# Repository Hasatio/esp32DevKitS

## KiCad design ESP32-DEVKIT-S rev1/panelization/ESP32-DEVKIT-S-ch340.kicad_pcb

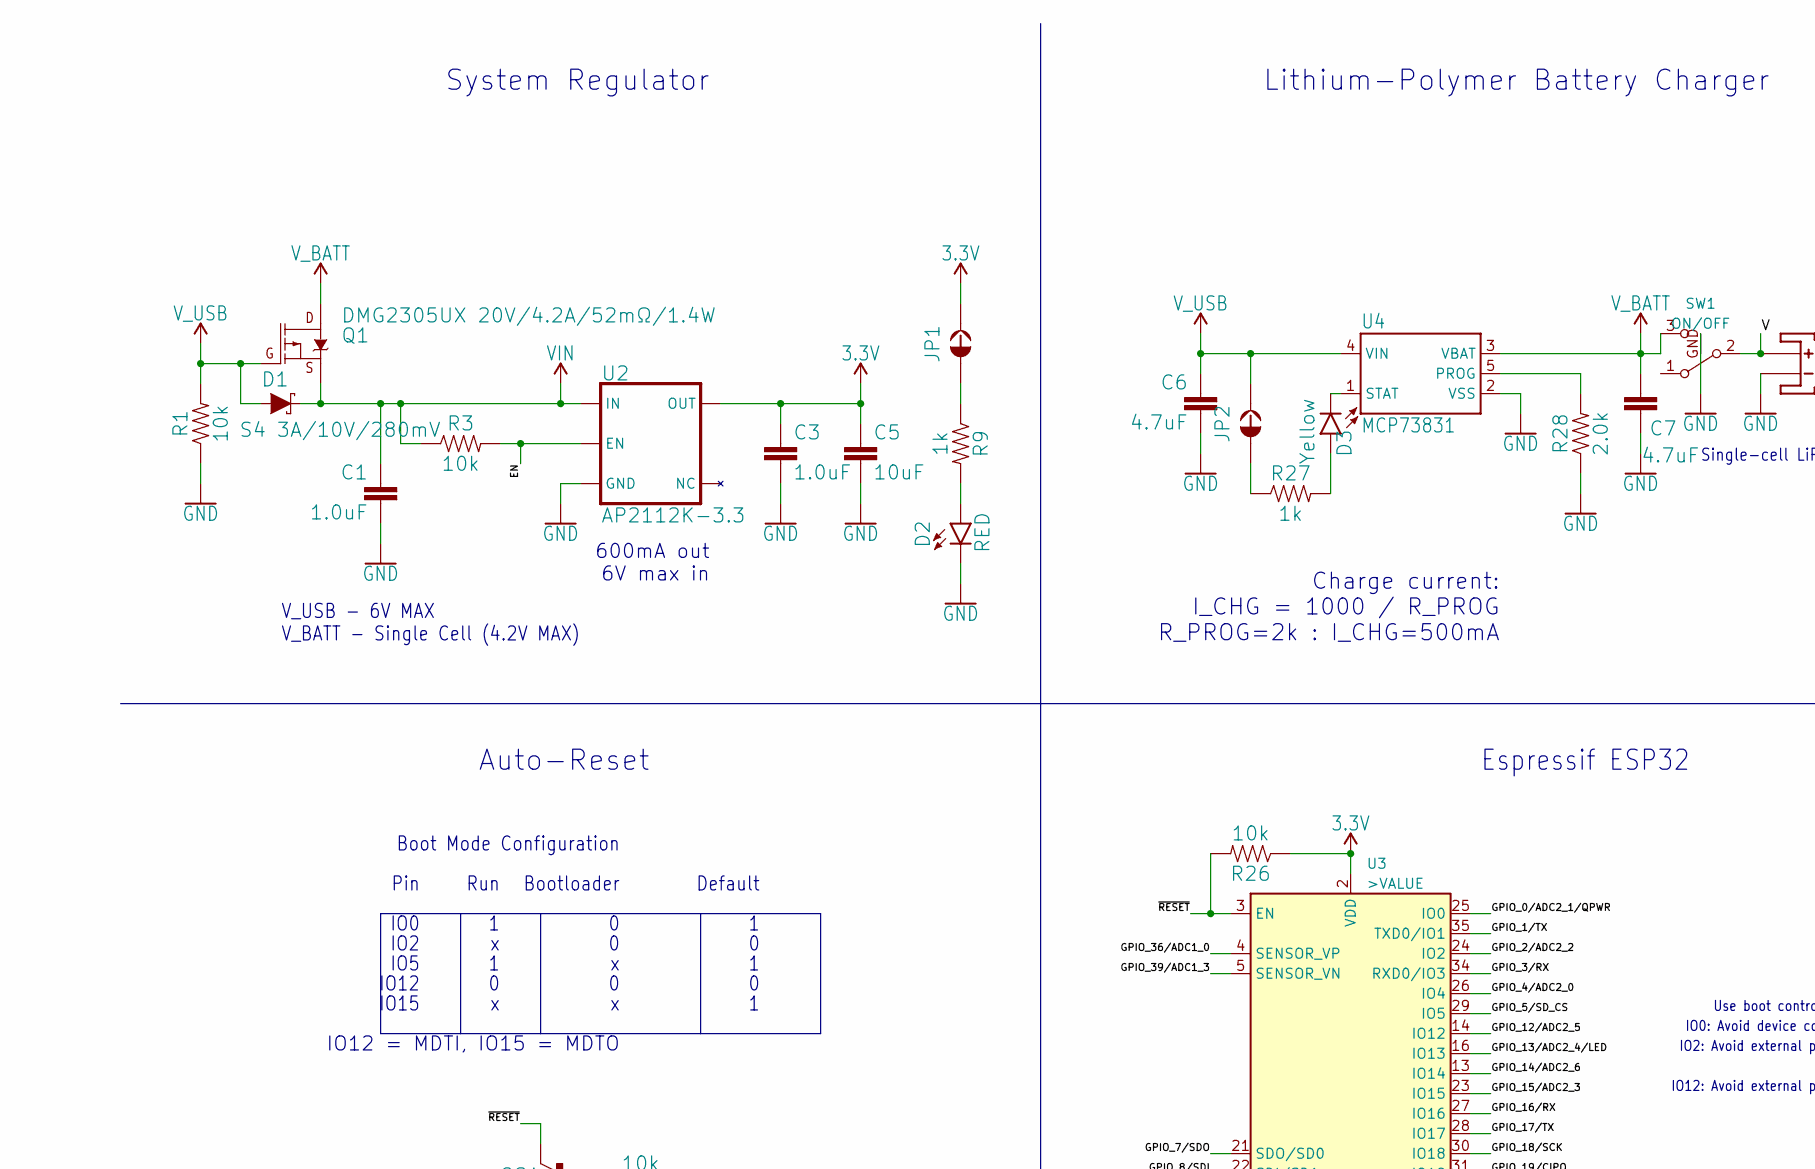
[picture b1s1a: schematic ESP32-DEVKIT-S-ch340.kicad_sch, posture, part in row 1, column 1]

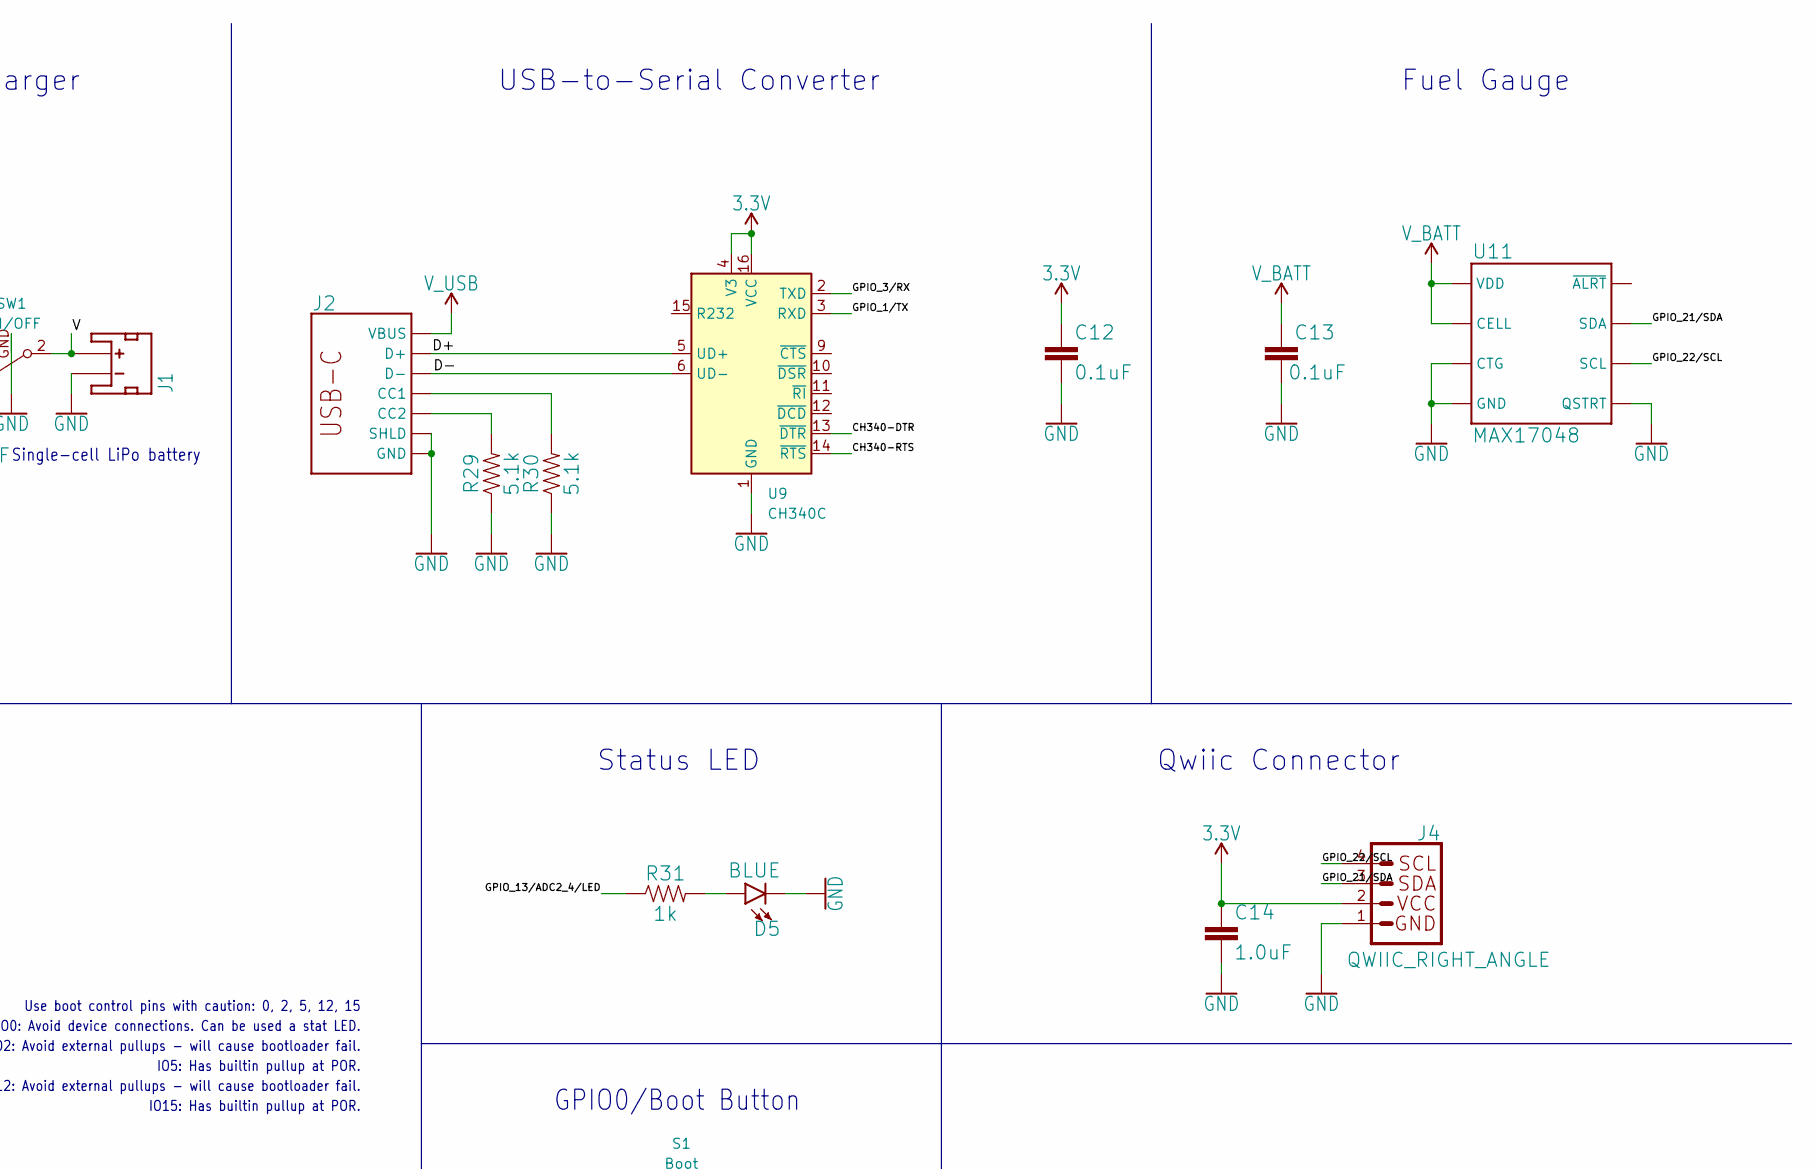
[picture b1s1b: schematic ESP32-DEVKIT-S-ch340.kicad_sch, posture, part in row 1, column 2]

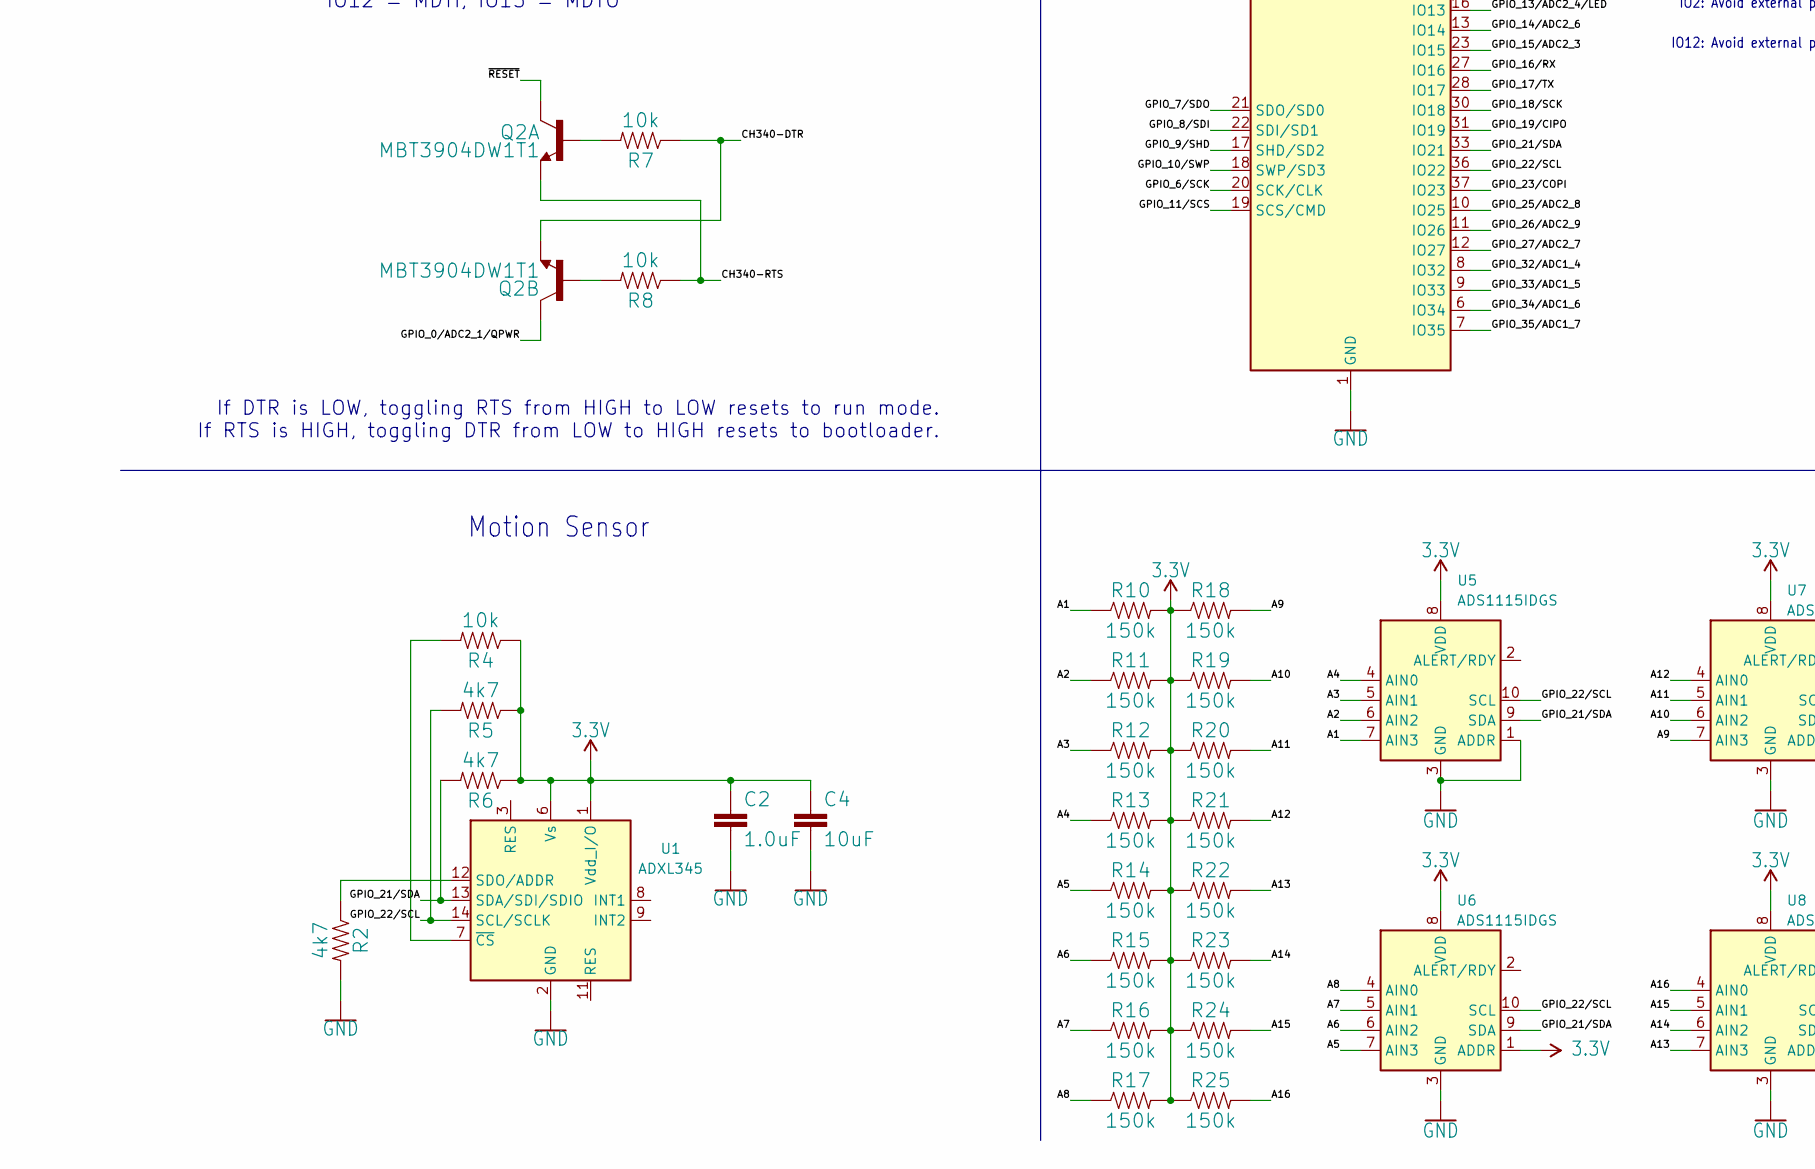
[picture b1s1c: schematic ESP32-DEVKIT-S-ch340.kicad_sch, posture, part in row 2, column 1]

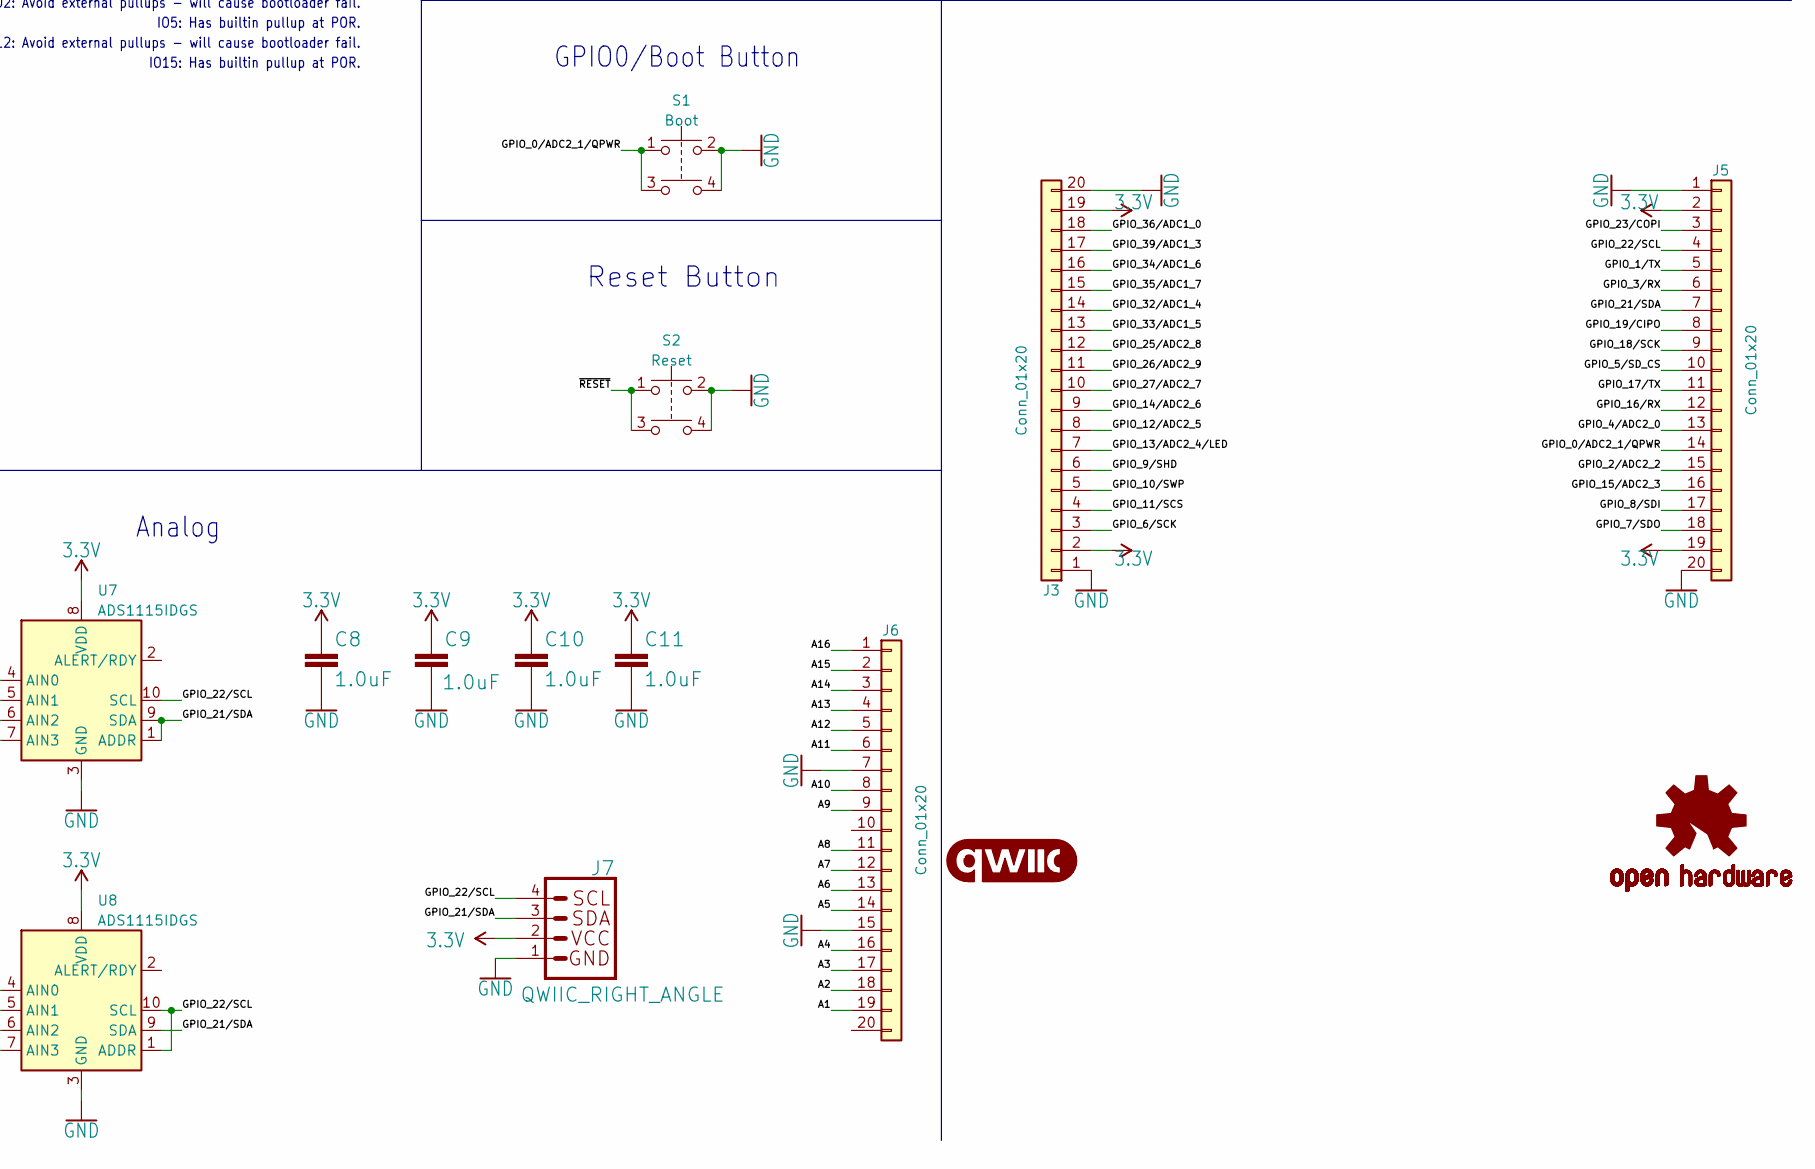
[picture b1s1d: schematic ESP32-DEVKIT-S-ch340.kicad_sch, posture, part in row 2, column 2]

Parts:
C1, C2, C3, C8, C9, C10, C11, C14: 1.0uF; 0402-TIGHT
C4, C5: 10uF; 0402-TIGHT
C6, C7: 4.7uF; 0402-TIGHT
C12, C13: 0.1uF; 0402-TIGHT
D1: S4 3A/10V/280mV; SOD-323
D2: RED; LED-0603
D3: Yellow; LED-0603
D5: BLUE; LED-0603
J1: JST_2MM_MALE; JST-2-SMD
J2: USB_C_2-LAYER_PADS; USB-C-16P-2LAYER-PADS
J3, J5, J6: Conn_01x20; Molex_200528-0200_1x20-1MP_P1.00mm_Horizontal
J4, J7: QWIIC_RIGHT_ANGLE; JST04_1MM_RA
JP1, JP2: JUMPER-SMT_2_NC_TRACE_SILK; SMT-JUMPER_2_NC_TRACE_SILK
LOGO1: QWIIC_LOGO_4MM; QWIIC_4MM
LOGO2: OSHW-LOGOMINI; OSHW-LOGO-MINI
Q1: DMG2305UX 20V/4.2A/52mΩ/1.4W; SOT23-3
Q2: MBT3904DW1T1; SC70-6
R1, R3, R4, R7, R8, R26: 10k; 0402-TIGHT
R2, R5, R6: 4k7; 0402-TIGHT
R9, R27, R31: 1k; 0402-TIGHT
R10, R11, R12, R13, R14, R15, R16, R17, R18, R19, R20, R21, R22, R23, R24, R25: 150k; 0402-TIGHT
R28: 2.0k; 0402-TIGHT
R29, R30: 5.1k; 0402-TIGHT
S1: Boot; TACTILE_SWITCH_SMD_2.8X1.9MM
S2: Reset; TACTILE_SWITCH_SMD_2.8X1.9MM
SW1: ON/OFF; SW_SPDT_k3-1295
U1: ADXL345; LGA-14_3x5mm_P0.8mm_LayoutBorder1x6y
U2: SOT23-5
U3: >VALUE; ESP-WROOM-32-NARROW
U4: MCP73831; SOT23-5
U5, U6, U7, U8: ADS1115IDGS; TSSOP-10_3x3mm_P0.5mm
U9: CH340C; SOIC-16_3.9x9.9mm_P1.27mm
U11: MAX17048; DFN-8

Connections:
3.3V: C2.1, C3.1, C4.1, C5.1, C8.1, C9.1, C10.1, C11.1, C12.1, C14.1, J3.2, J3.19, J4.2, J5.2, J5.19, J7.2, JP1.2, R4.1, R5.1, R6.1, R10.2, R11.2, R12.2, R13.2, R14.2, R15.2, R16.2, R17.2, R18.1, R19.1, R20.1, R21.1, R22.1, R23.1, R24.1, R25.1, R26.1, U1.1 (Vdd_I/O), U1.6 (Vs), U2.5 (OUT), U3.2 (VDD), U5.8 (VDD), U6.1 (ADDR), U6.8 (VDD), U7.8 (VDD), U8.8 (VDD), U9.4 (V3), U9.16 (VCC); also elsewhere on the board
/A1: J6.19, R10.1, U5.7 (AIN3); also elsewhere on the board
/A2: J6.18, R11.1, U5.6 (AIN2); also elsewhere on the board
/A3: J6.17, R12.1, U5.5 (AIN1); also elsewhere on the board
/A4: J6.16, R13.1, U5.4 (AIN0); also elsewhere on the board
/A5: J6.14, R14.1, U6.7 (AIN3); also elsewhere on the board
/A6: J6.13, R15.1, U6.6 (AIN2); also elsewhere on the board
/A7: J6.12, R16.1, U6.5 (AIN1); also elsewhere on the board
/A8: J6.11, R17.1, U6.4 (AIN0); also elsewhere on the board
/A9: J6.9, R18.2, U7.7 (AIN3); also elsewhere on the board
/A10: J6.8, R19.2, U7.6 (AIN2); also elsewhere on the board
/A11: J6.6, R20.2, U7.5 (AIN1); also elsewhere on the board
/A12: J6.5, R21.2, U7.4 (AIN0); also elsewhere on the board
/A13: J6.4, R22.2, U8.7 (AIN3); also elsewhere on the board
/A14: J6.3, R23.2, U8.6 (AIN2); also elsewhere on the board
/A15: J6.2, R24.2, U8.5 (AIN1); also elsewhere on the board
/A16: J6.1, R25.2, U8.4 (AIN0); also elsewhere on the board
/CH340-DTR: Q2.1 (E), R7.1, U9.13 (~DTR)
/CH340-RTS: Q2.4 (E), R8.1, U9.14 (~RTS)
/D+: J2.A6 (D+), J2.B6 (D+), U9.5 (UD+)
/D-: J2.A7 (D-), J2.B7 (D-), U9.6 (UD-)
/EN: R3.2, U2.3 (EN)
/GPIO_0/ADC2_1/QPWR: J5.14, Q2.6 (C), S1.1, S1.3, U3.25 (IO0)
/GPIO_2/ADC2_2: J5.15, U3.24 (IO2)
/GPIO_4/ADC2_0: J5.13, U3.26 (IO4)
/GPIO_5/SD_CS: J5.10, U3.29 (IO5)
/GPIO_6/SCK: J3.3, U3.20 (SCK/CLK)
/GPIO_7/SDO: J5.18, U3.21 (SDO/SD0)
/GPIO_8/SDI: J5.17, U3.22 (SDI/SD1)
/GPIO_9/SHD: J3.6, U3.17 (SHD/SD2)
/GPIO_10/SWP: J3.5, U3.18 (SWP/SD3)
/GPIO_11/SCS: J3.4, U3.19 (SCS/CMD)
/GPIO_12/ADC2_5: J3.8, U3.14 (IO12)
/GPIO_13/ADC2_4/LED: J3.7, R31.1, U3.16 (IO13)
/GPIO_14/ADC2_6: J3.9, U3.13 (IO14)
/GPIO_15/ADC2_3: J5.16, U3.23 (IO15)
/GPIO_16/RX: J5.12, U3.27 (IO16)
/GPIO_17/TX: J5.11, U3.28 (IO17)
/GPIO_18/SCK: J5.9, U3.30 (IO18)
/GPIO_19/CIPO: J5.8, U3.31 (IO19)
/GPIO_21/SDA: J4.3, J5.7, J7.3, R6.2, U1.13 (SDA/SDI/SDIO), U3.33 (IO21), U5.9 (SDA), U6.9 (SDA), U7.1 (ADDR), U7.9 (SDA), U8.9 (SDA), U11.8 (SDA); also elsewhere on the board
/GPIO_22/SCL: J4.4, J5.4, J7.4, R5.2, U1.14 (SCL/SCLK), U3.36 (IO22), U5.10 (SCL), U6.10 (SCL), U7.10 (SCL), U8.1 (ADDR), U8.10 (SCL), U11.7 (SCL); also elsewhere on the board
/GPIO_23/COPI: J5.3, U3.37 (IO23)
/GPIO_25/ADC2_8: J3.12, U3.10 (IO25)
/GPIO_26/ADC2_9: J3.11, U3.11 (IO26)
/GPIO_27/ADC2_7: J3.10, U3.12 (IO27)
/GPIO_32/ADC1_4: J3.14, U3.8 (IO32)
/GPIO_33/ADC1_5: J3.13, U3.9 (IO33)
/GPIO_34/ADC1_6: J3.16, U3.6 (IO34)
/GPIO_35/ADC1_7: J3.15, U3.7 (IO35)
/GPIO_36/ADC1_0: J3.18, U3.4 (SENSOR_VP)
/GPIO_39/ADC1_3: J3.17, U3.5 (SENSOR_VN)
/V: J1.2 (+), SW1.2 (B)
/~RESET: Q2.3 (C), R26.2, S2.1, S2.3, U3.3 (EN)
GND: C1.2, C2.2, C3.2, C4.2, C5.2, C6.2, C7.2, C8.2, C9.2, C10.2, C11.2, C12.2, C13.2, C14.2, D2.C, D5.C, J1.1 (-), J2.GND, J2.GND2 (GND), J2.SHLD1 (SHLD), J2.SHLD2 (SHLD), J2.SHLD3 (SHLD), J2.SHLD4 (SHLD), J3.1, J3.20, J4.1, J5.1, J5.20, J6.7, J6.15, J7.1, R1.1, R2.2, R28.1, R29.1, R30.1, S1.2, S1.4, S2.2, S2.4, SW1.GND, U1.2 (GND), U1.4 (GND), U1.5 (GND), U2.2 (GND), U3.1 (GND), U3.15 (GND), U3.38 (GND), U3.39 (GND), U4.2 (VSS), U5.1 (ADDR), U5.3 (GND), U6.3 (GND), U7.3 (GND), U8.3 (GND), U9.1 (GND), U11.1 (CTG), U11.4 (GND), U11.6 (QSTRT), U11.9 (GND); also elsewhere on the board
unnamed: D2.A, R9.2
unnamed: D3.A, R27.2
unnamed: D5.A, R31.2
unnamed: J2.A5 (CC1), R30.2
unnamed: J2.B5 (CC2), R29.2
unnamed: JP1.1, R9.1
unnamed: JP2.1, R27.1
unnamed: Q2.5 (B), R7.2
unnamed: Q2.2 (B), R8.2
unnamed: R2.1, U1.12 (SDO/ADDR)
unnamed: R4.2, U1.7 (~CS)
unnamed: R28.2, U4.5 (PROG)
unnamed: D3.C, U4.1 (STAT)
VIN: C1.1, D1.C, Q1.2 (S), R3.1, U2.1 (IN), U2.4 (NC)
V_BATT: C7.1, C13.1, Q1.3 (D), SW1.3 (C), U4.3 (VBAT), U11.2 (CELL), U11.3 (VDD)
V_USB: C6.1, D1.A, J2.VBUS1 (VBUS), J2.VBUS2 (VBUS), JP2.2, Q1.1 (G), R1.2, U4.4 (VIN)

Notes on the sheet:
Fuel Gauge
Auto-Reset
IO15
Boot Mode Configuration
Reset Button
Default
Pin
IO5: Has builtin pullup at POR.
IO5
Run
Qwiic Connector
IO0
V_USB - 6V MAX V_BATT - Single Cell (4.2V MAX)
Lithium-Polymer Battery Charger
IO2
IO12: Avoid external pullups - will cause bootloader fail.
Espressif ESP32
IO12
USB-to-Serial Converter
IO15: Has builtin pullup at POR.
Motion Sensor
Analog
Status LED
Bootloader
Use boot control pins with caution: 0, 2, 5, 12, 15
GPIO0/Boot Button
Single-cell LiPo battery
Charge current: I_CHG = 1000 / R_PROG R_PROG=2k : I_CHG=500mA
IO0: Avoid device connections. Can be used a stat LED.
600mA out 6V max in
If DTR is LOW, toggling RTS from HIGH to LOW resets to run mode. If RTS is HIGH, toggling DTR from LOW to HIGH resets to bootloader.
IO2: Avoid external pullups - will cause bootloader fail.
IO12 = MDTI, IO15 = MDTO
System Regulator

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
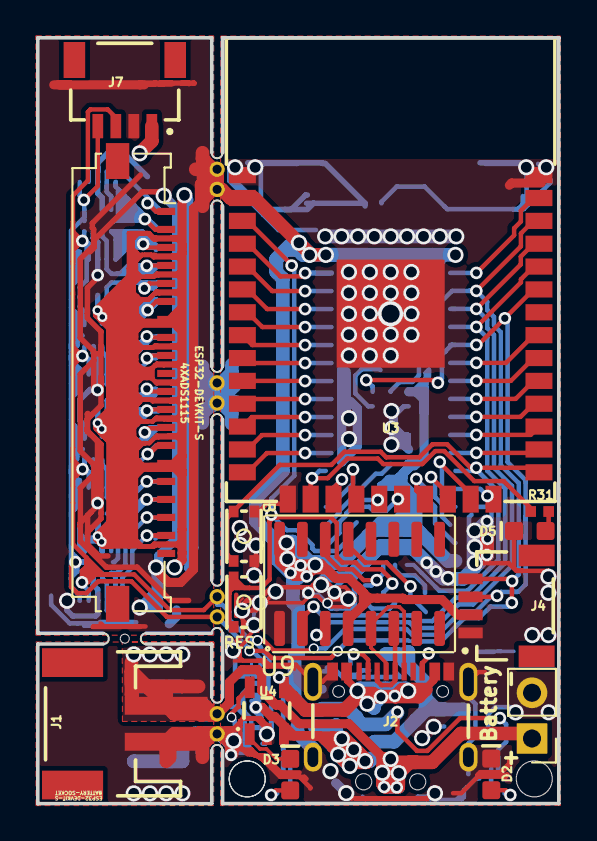
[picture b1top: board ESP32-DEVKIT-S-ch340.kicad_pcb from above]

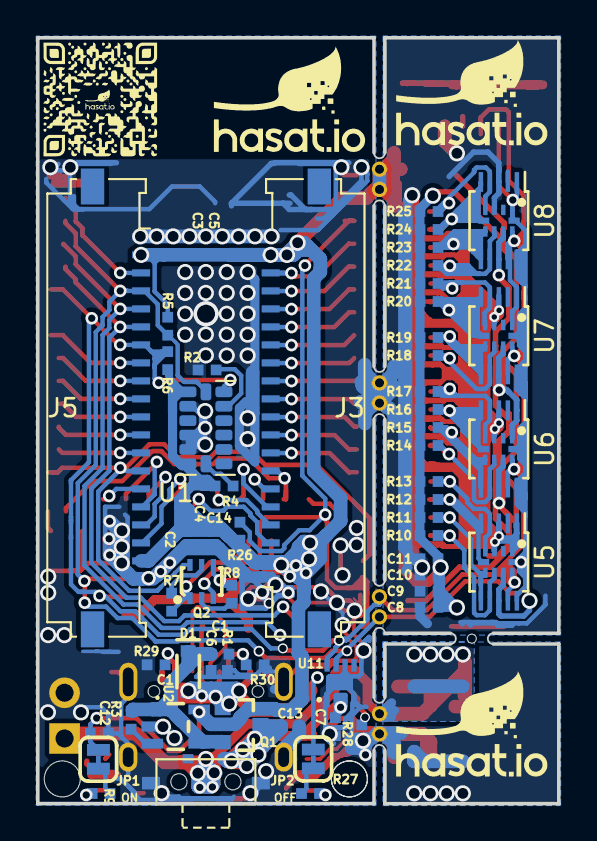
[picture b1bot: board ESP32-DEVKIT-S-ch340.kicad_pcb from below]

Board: 2 copper layers, 28.9 x 42.5 mm, 83 parts (63 on the bottom side), 73 nets.

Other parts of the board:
>NAME: >VALUE; QFN-10-RSE
>NAME#2, >NAME#3, >NAME#4: >VALUE; QFN-10-RSE
FRAME1: FRAME-LEDGER; CREATIVE_COMMONS
mouse-bite-1mm-slot: VAL**; mouse-bite-1mm x2
mouse-bite-emm-slot: VAL**; mouse-bite-1mm 2
mouse-bite-emm-slot#2, mouse-bite-emm-slot#3, mouse-bite-emm-slot#4: VAL**; mouse-bite-1mm 2

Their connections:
3.3V: >NAME.8, >NAME#2.8, >NAME#3.1, >NAME#3.8, >NAME#4.8; also elsewhere on the board
/A1: >NAME#4.7; also elsewhere on the board
/A2: >NAME#4.6; also elsewhere on the board
/A3: >NAME#4.5; also elsewhere on the board
/A4: >NAME#4.4; also elsewhere on the board
/A5: >NAME#3.7; also elsewhere on the board
/A6: >NAME#3.6; also elsewhere on the board
/A7: >NAME#3.5; also elsewhere on the board
/A8: >NAME#3.4; also elsewhere on the board
/A9: >NAME.7; also elsewhere on the board
/A10: >NAME.6; also elsewhere on the board
/A11: >NAME.5; also elsewhere on the board
/A12: >NAME.4; also elsewhere on the board
/A13: >NAME#2.7; also elsewhere on the board
/A14: >NAME#2.6; also elsewhere on the board
/A15: >NAME#2.5; also elsewhere on the board
/A16: >NAME#2.4; also elsewhere on the board
/GPIO_21/SDA: >NAME.1, >NAME.9, >NAME#2.9, >NAME#3.9, >NAME#4.9; also elsewhere on the board
/GPIO_22/SCL: >NAME.10, >NAME#2.1, >NAME#2.10, >NAME#3.10, >NAME#4.10; also elsewhere on the board
GND: >NAME.3, >NAME#2.3, >NAME#3.3, >NAME#4.1, >NAME#4.3; also elsewhere on the board
